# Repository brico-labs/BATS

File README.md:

NOTA IMPORTANTE  
Lee a sección [META](#meta) para clonar este proxecto.

Qué imos facer? Qué se describe en este documento?
==================================================

Imos deseñar un shield para Arduino usando [KiCad](http://www.kicad-pcb.org/)

Daremos unha visión xeral da funcionalidade da suite KiCad pero non vamos a redactar un tutorial detallado nin de deseño de circuitos nin do mesmo KiCad. Daremos as pistas xustiñas para empezar a traballar con KiCad, se queredes un tutorial detallado, en youtube tedes un super recomendable, elaborado por [TutoElectro](https://www.youtube.com/playlist?list=PL1Hs_F1k2mdRVYDtdWd7tQKDZTfxop7np)

Tamén comentaremos a nivel xeral os pasos para desenvolver este proxecto.

Qué é KiCad?
============

KiCad é unha suite de deseño electrónico automatizado [1]. KiCad permite o deseño tanto de esquemas de circuitos como das placas de circuito impreso a nivel profesional. A suite está dispoñible para Windows, Linux e Apple OS X. É un programa gratuito e **libre** distribuido baixo licencia **GNU GPL v2**.

Mellor ainda, a suite KiCad é a elexida polo CERN para o desenvolvemento e deseño de electrónica. É de esperar que con este respaldo a suite mellore ainda mais.

Requisitos do shield
====================

Queremos facer un shield que poida servir para iniciarse no mundo da programación con Arduino, especialmente centrado no ensino (tecnoloxía 3º - 4º ESO). Neste eido, traballar sobre breadboard pode ser complexo, moitas veces o material é compartido e isto implica que, cada clase, hai que montar e desmontar o circuito que logo se programará. Isto leva o seu tempo e ocasiona erros de montaxe que son difíciles de detectar, polo que o uso dun shield parece que pode ser unha solución.

Mália isto, empregando un shield xa ensamblada se perde a oportunidade de profundizar os coñecementos de electrónica e circuitos que se adquiren ao facer un mesmo a montaxe, así que un shield na que o alumno/a teña que colocar e soldar el mesmo os compoñentes, segundo avanza na súa aprendizaxe, parécenos a solución de compromiso idónea.

Queremos que o shield sexa escalable, que sirva para traballar cuns poucos compoñentes se non se quere profundizar demasiado, pero que permita tamén chegar a nivéis máis avanzados e con máis compoñentes sen cambiar de shield.

Estes son os compoñentes que se pensan incluír:

-   3-4 x Botóns
-   1 x RGB
-   1 x LDR
-   1 x Pines servo
-   1 x sensor temp (dudoso)
-   2 x potenciómetros
-   1 x LED vermello
-   1 x LED amarelo
-   1 x LED verde
-   1 x Zoador
-   1 x Botón de reset

Instalación de KiCad (en Ubuntu)
================================

Para instalar o KiCad en Ubuntu basta con facer o típico ciclo de instalación:

``` {bash}
sudo apt-get install kicad
```

Se queremos estar á última temos o ppa de Monsieur Reynaud dispoñible:

``` {bash}
sudo apt-add-repository ppa:js-reynaud/ppa-KiCad
sudo apt-get update
sudo apt-get install kicad
```

Nos escollimos esta opción.

Se non usades un linux baseado en Debian, teredes que consultar na rede como facer a instalación para o voso sistema operativo. De todolos xeitos a instalación é moi doada, donde podemos atopar algún problemiña é na instalación das bibliotecas de compoñentes que vos contaremos cos mais detalle mais adiante.

Configuración de directorios para este proxecto
===============================================

Además de desenvolver o proxecto con KiCad queremos ter o proxecto dispoñible en github.

Agora que temos KiCad instalado imos preparar un directorio de traballo ao que chamamos **bats**.

O directorio **bats** será o "repositorio" ou depósito do noso proxecto para git. Contén os seguintes subdirectorios:

doc  
Contén a documentación do proxecto (o que estás a leer agora mesmo) redactada en [Pandoc](http://pandoc.org/)

kicad  
Contén o proxecto KiCad

Unha vez que temos preparado o directorio do proxecto activamos git para iniciar o control de versións.

------------------------------------------------------------------------

Describir a configuración de git??

------------------------------------------------------------------------

Biblioteca de compoñentes incluindo un shield para Arduino
==========================================================

As bibliotecas de KiCad están organizadas en duas partes:

-   Un ficheiro que contén os símbolos dos compoñentes para usarse no editor de esquemas electrónicos **Eescheme**

-   As pegadas dos compoñentes electrónicos, é dicir, a forma que ten que ter a pista da placa de circuito impreso (*PCB*) para poder soldar o compoñente.

O KiCad trae por defecto varios templates que permiten o desenrolo de proxectos baseados en diferentes modelos de Arduino.

Nos optamos por outro camiño, instalamos unha nova biblioteca de compoñentes e fixemos o proxecto usando esta biblioteca.

Unha biblioteca moi completa é a de Freetronics que podemos atopar tamén en github en:

<https://github.com/freetronics/freetronics_KiCad_library.git>

As bibliotecas de KiCad poden estar almacenadas en diferentes directorios do noso ordenador. Poderíamos engadir as bibliotecas que usemos en algún subdirectorio de */usr/share/kicad* ou de */usr/local/share*. Esta podería ser unha boa estratexia nun servidor compartido por varios usuarios. Tamén poderíamos descarregar todas as bibliotecas a un directorio común do noso *home*. Pero como estamos facendo un control de versións do noso proxecto con git a propia páxina da biblioteca suxírenos o xeito mais adoitado de facer a instalación: coma un submódulo git do noso proxecto.

A vantaxe de engadir a biblioteca de compoñentes de Freetronics coma un submódulo Git é que o noso proxecto queda "aillado" do proxecto engadido como submódulo. Podemos avanzar no noso proxecto e salvar os cambios feitos con Git, sen afectar aos submódulos, e viceversa.

Por exemplo, unha vez que teñamos o noso directorio de traballo configurado con git, e a libreria de Freetronics engadida como submodulo, poderíamos empezar o desenrolo da nosa placa BATS e ir gardando os nosos avances. Estas operacións non afectarán a librería Freetronics, que de feito ainda que esta descarregada no noso directorio de traballo, non está gardada no git do noso proxecto, soamente está enlazada.

Se no futuro nos interesa actualizarnos a unha versión mais avanzada da librería Freetronics, podemos facer un commit do noso proxecto nunha situación controlada, e despois actualizar o submodulo correspondiente a librería.

Engadir a biblioteca como un submódulo de git
---------------------------------------------

Dende o directorio principal de noso proxecto descarregamos a biblioteca de Freetronics coma un submodulo do noso proxecto:

``` {bash}
cd kicad 
git submodule add https://github.com/freetronics/freetronics_kicad_library.git kicad/ftlibrary
```

Despois de engadir a biblioteca como un submódulo se consultamos o estado git do noso proxecto aparecerán dous novos ficheiros:

``` {bash}
$ git status
On branch master
Your branch is up-to-date with 'origin/master'.
Changes to be committed:
  (use "git reset HEAD <file>..." to unstage)

    new file:   .gitmodules
    new file:   kicad/ftlibrary
```

Git engadíu automáticamente os dous novos ficheiros, o directorio que contén a nosa biblioteca eo ficheiro **.gitmodule** que levará o control de todolos submódulos que usemos.

En realidade os ficheiros que compoñen a biblioteca non pertencen ao noso depósito de software, git só leva conta da versión da biblioteca de Freetronics que estamos a usar.

Se queres saber mais de esta potente funcionalidade de git podes leer: <http://www.git-scm.com/book/en/v2/Git-Tools-Submodules>

Configurar *Eescheme* para usar a nova biblioteca
-------------------------------------------------

No menú Preferences -&gt; Component Library sinalamos na fiestra inferior o directorio do noso proxecto. Na fiestra superior engadimos o ficheiro da biblioteca.

No github da biblioteca nos aconsellan poñer a biblioteca de primeira na nosa lista por que definen todo tipo de compoñentes. Nos de momento seguimos o consello de Freetronics, e a puxemos de primeira.

Configurar acceso aos datos de pegadas (*footprints*) en pcbnew
---------------------------------------------------------------

Configuramos un ficheiro para o noso proxecto declarando os *footprint* extra que imos a utilizar.

``` {cpp}
(fp_lib_table
  (lib
   (name FT)
   (type KiCad)
   (uri ${KIPRJMOD}/ftlibrary/freetronics_footprints.pretty)
   (options "")
   (descr "Freetronics Kicad Library")
   )
)
```

Engadimos o novo ficheiro ao noso repositorio

``` {bash}
git add fp-lib-table
```

Abrimos *Pcbnew* e no menú *Preferences-&gt;Footprint Libraries Manager* comprobamos que na pestaña *Project Specific Libraries* figura o noso ficheiro.

Tutorial
========

Checklist: Pasos a seguir para rematar o proxecto
-------------------------------------------------

-   Abrir o proxecto (e mellor tér un directorio dedicado ao proxecto creado en adianto)
-   Crear o esquema do circuito (usando Eescheme)
-   Chequeo de erros (opción *Perform Electrical Rules Check*)
-   Asignar as pegadas (*footprints*) aos compoñentes (opción *run CvPcb* dende o *Eescheme*). As pegadas quedan asignadas a cada compoñente no esquema.
-   Xerar o ficheiro NET (opción *Generate netlist*)
-   Abrir o PcbNew e cargar o ficheiro NET xenerado dende o Eescheme
-   Distribuir os compoñentes do noso proxecto intentado simplificar a topoloxía das pistas o que poidamos.

A pantalla xeral
----------------

------------------------------------------------------------------------

Pantalla xeral de KiCad opcións, citar a lista de hotkeys

------------------------------------------------------------------------

Abrindo un proxecto
-------------------

### Checklist

-   Usar un directorio adicado ao proxecto
-   Engadir a información do proxecto ao esquema.

Abrimos un novo proxecto: File::New Project (Ctrl+N) **bats**

### 

Crear e Editar o esquema do circuito
------------------------------------

O primeiro que imos facer é o esquema do circuito. Para isto temos que usar a ferramenta *Eeschema* que podemos atopar en tres lugares diferentes [2] na barra de iconos de ferramentas, no menú de KiCad no título da fiestra, ou có atallo **Ctrl+E**.

Abrimos eescheme e creamos un novo ficheiro de esquema.

ERC: comprobación dos erros no circuito
---------------------------------------

### Tips

-   Falar dos flags
    -   Power flags
    -   Not used flag
-   Falar dos ficheiros de pegadas
-   Falar da asignación automática de pegadas

As bibliotecas en KiCAD
=======================

Esta é sen dúbida a parte de KiCAD mais criticada. Hai varias razóns para isto:

-   As bibliotecas de KiCAD manteñen separados os símbolos dos compoñentes para usar no esquema do circuito das pegadas (*footprints*) dos mesmos que son os que se usan no deseño da placa.
-   Os símbolos dos compoñentes están almacenados en ficheiros con extensión *.lib* de ahí que con frecuencia se lles chame *library* (traducido librerias) na xerga de KiCAD
-   Por contra as pegadas dos compoñentes almacénanse en ficheiros con extensión *.mod* ou as mais modernas *.kicad\_mod* de ahí que a miudo se lles chame *modules* (traducido módulos) na xerga de KiCAD
-   Os menús e diálogos para engadir ficheiros *.lib* e os ficheiros *.mod* son completamente diferentes
-   KiCAD soporta multiples localizacións para as bibliotecas, mesmo localizacións en github.

Dende o noso punto de vista o mais sinxelo e ter un só directorio donde almacenemos as bibliotecas de terceiros que queremos usar con KiCAD. Nos usamos **~/resources/kicad** de feito temos:

~/resources/kicad/my\_kicad\_lib  
Para os compoñentes de diseño propio

~/resources/kicad/my\_kicad.pretty  
para os footprints de diseño propio

~/resources/kicad/kicad\_3rd  
para librerias de terceiros

Un exemplo: Engadir novas bibliotecas Arduino
---------------------------------------------

Imos ver como engadir unha nova biblioteca de compoñentes de xeito global (quedará dispoñible para todos os proxectos) ou só para un proxecto concreto.

As bibliotecas que imos usar pódense atopar en esta [páxina](http://meta-blog.eklablog.com/kicad-librairie-arduino-pretty-p930786).

Na páxina hai dous ficheiros dispoñibles para descarga. O que contén as plantillas (*templates*) non o queremos, xa está incluido no github de KiCAD.

Descarregamos o outro e descomprimimos no directorio donde imos ter as bibliotecas de KiCAD, no noso caso: **~/resources/kicad/kicad\_3rd**

Enlaces útiles
==============

-   [Conceptos de circuitos impresos](http://www.pcb.electrosoft.cl/04-articulos-circuitos-impresos-desarrollo-sistemas/01-conceptos-circuitos-impresos/conceptos-circuitos-impresos-pcb.html)
-   [Instalación das bibliotecas](http://www.arunet.co.uk/tkboyd/ele2pcbka.htm)
-   [Mais bibliotecas para KiCad](http://www.kicadlib.org/)

Dende o seguinte enlace podese descarregar unha biblioteca de compoñentes moi currada, ainda que algo anticuada:

<git://smisioto.eu/KiCad_libs.git>

META
====

Este repositorio usa submódulos de git para a xestión das bibliotecas de compoñentes. Para clonar o repositorio tes que clonar o repositorio e despois actualizar os submódulos executando:

``` {bash}
$ git clone https://github.com/brico-labs/BATS
$ git submodule update --init
```

Este documento está escrito en [Markdown-Pandoc](http://pandoc.org/README.html). Pandoc e un sistema moi sinxelo de documentación que permite xerar multiples formatos de saída.

As fontes do documento están no directorio **doc/src**. Os formatos de saída son este fichero **README.md** en formato Markdown-github e os documentos que podes atopar no directorio **doc/out** incluindo un pdf.

Os documentos xéranse automáticamente a partir do ficheiro fonte sen mais que executar:

``` {bash}
$ cd doc
$ make
```

Outras opcións que soporta o **makefile** serían **reset** para rexerar todos os documentos de saída por defecto, **odt** para xerar un **bats\_gl.odt**.

``` {bash}
$ make reset
$ make odt
```

[1] EDA suite en inglés

[2] Isto de ter varios xeitos de facer unha cousa é habitual en KiCad como iremos vendo

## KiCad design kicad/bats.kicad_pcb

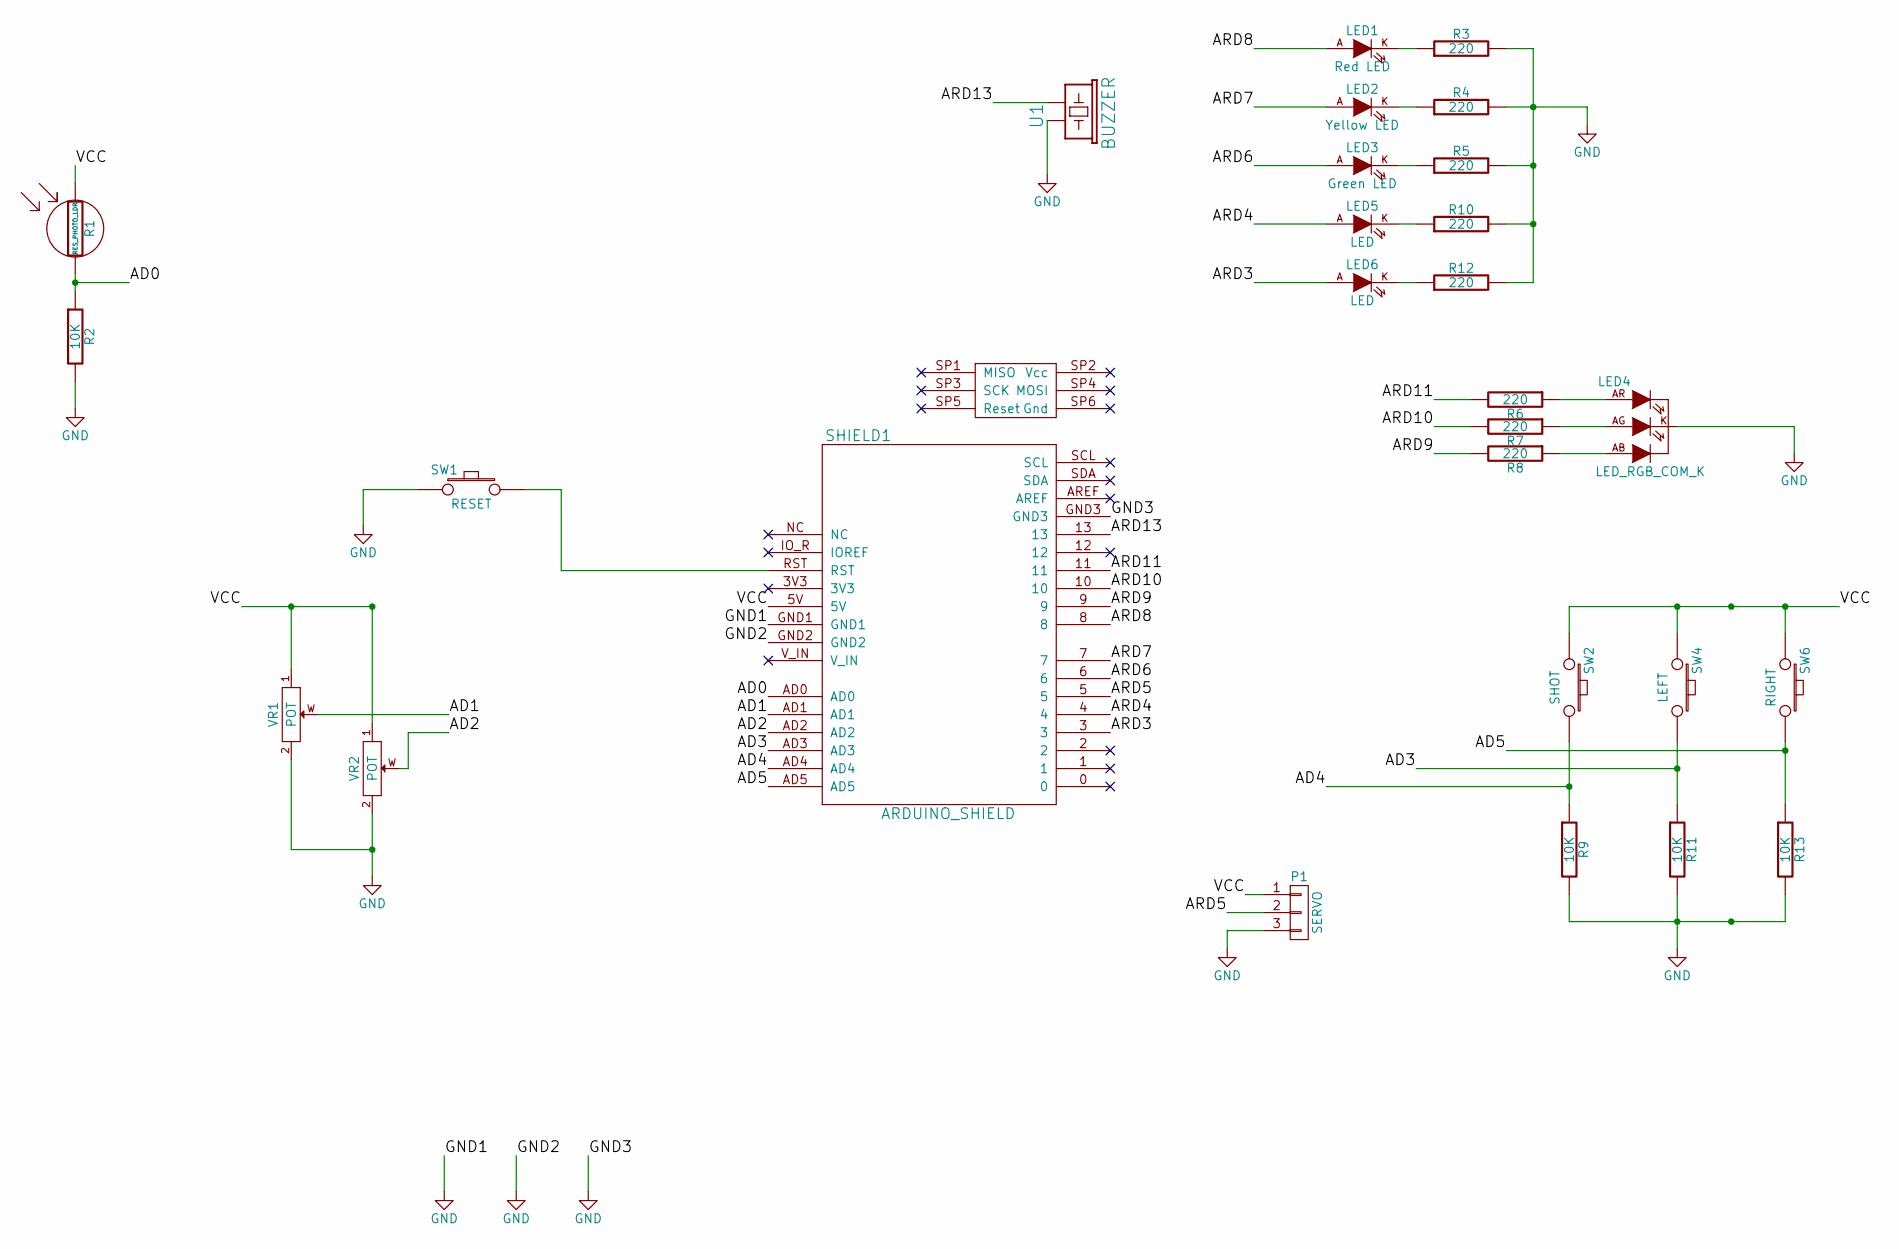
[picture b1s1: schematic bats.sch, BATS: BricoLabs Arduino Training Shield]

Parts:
LED1: Red LED; LED-5MM_easy_soldering
LED2: Yellow LED; LED-5MM_easy_soldering
LED3: Green LED; LED-5MM_easy_soldering
LED4: LED_RGB_COM_K; LED-RGB-8MM-COM-K-MINIMAL
LED5, LED6: LED; LED-5MM_easy_soldering
P1: SERVO; 1X03
R1: RES_PHOTO_LDR; Resistor_Horizontal_SmallHole_RM10mm
R2, R9, R11, R13: 10K; Resistor_Horizontal_SmallHole_RM10mm
R3, R4, R5, R6, R7, R8, R10, R12: 220; Resistor_Horizontal_SmallHole_RM10mm
SHIELD1: ARDUINO_SHIELD
SW1: RESET; SW_PUSHBUTTON_PTH
SW2: SHOT; SW_PUSHBUTTON_PTH
SW4: LEFT; SW_PUSHBUTTON_PTH
SW6: RIGHT; SW_PUSHBUTTON_PTH
U1: BUZZER; Buzzer_12x9.5RM7.6
VR1, VR2: POT; POT_RV09_VERT_easySoldering

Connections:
/AD0: R1.2, R2.1, SHIELD1.AD0
/AD1: SHIELD1.AD1, VR1.W
/AD2: SHIELD1.AD2, VR2.W
/AD3: R11.1, SHIELD1.AD3, SW4.2
/AD4: R9.1, SHIELD1.AD4, SW2.2
/AD5: R13.1, SHIELD1.AD5, SW6.2
/ARD3: LED6.A, SHIELD1.3
/ARD4: LED5.A, SHIELD1.4
/ARD5: P1.2, SHIELD1.5
/ARD6: LED3.A, SHIELD1.6
/ARD7: LED2.A, SHIELD1.7
/ARD8: LED1.A, SHIELD1.8
/ARD9: R8.2, SHIELD1.9
/ARD10: R7.2, SHIELD1.10
/ARD11: R6.2, SHIELD1.11
/ARD13: SHIELD1.13, U1.2 (GND)
/VCC: P1.1, R1.1, SHIELD1.5V, SW2.1, SW4.1, SW6.1, VR1.1, VR2.1
GND: LED4.K, P1.3, R2.2, R3.2, R4.2, R5.2, R9.2, R10.2, R11.2, R12.2, R13.2, SHIELD1.GND1, SHIELD1.GND2, SHIELD1.GND3, SW1.1, U1.1 (POS), VR1.2, VR2.2
unnamed: LED1.K, R3.1
unnamed: LED2.K, R4.1
unnamed: LED3.K, R5.1
unnamed: LED4.AB, R8.1
unnamed: LED4.AG, R7.1
unnamed: LED4.AR, R6.1
unnamed: LED5.K, R10.1
unnamed: LED6.K, R12.1
unnamed: SHIELD1.RST, SW1.2

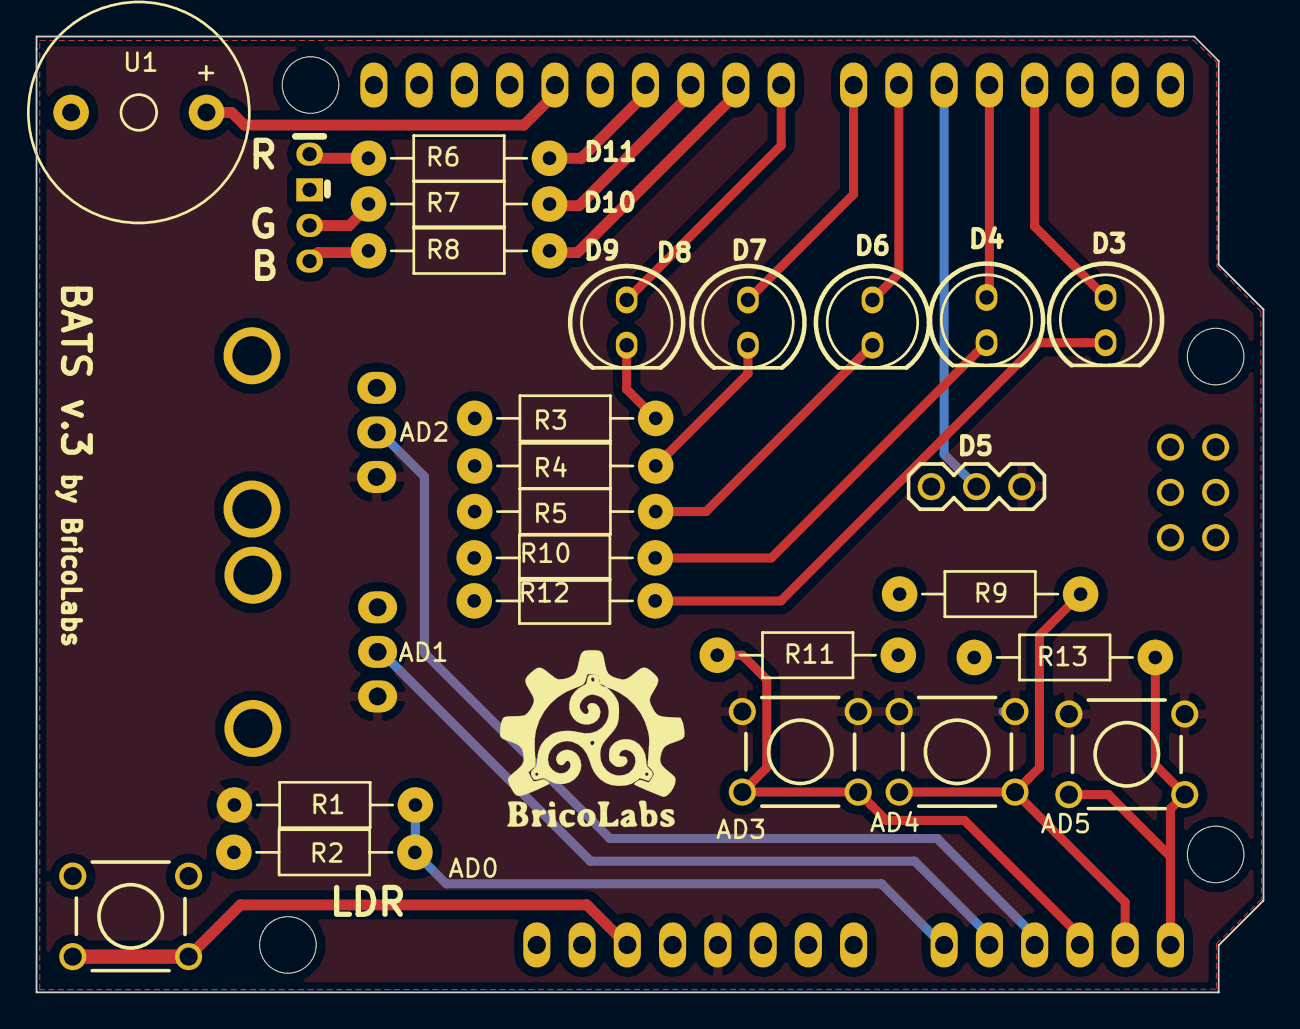
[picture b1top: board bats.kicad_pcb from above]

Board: 2 copper layers, 68.9 x 53.6 mm, 28 parts (0 on the bottom side), 27 nets.

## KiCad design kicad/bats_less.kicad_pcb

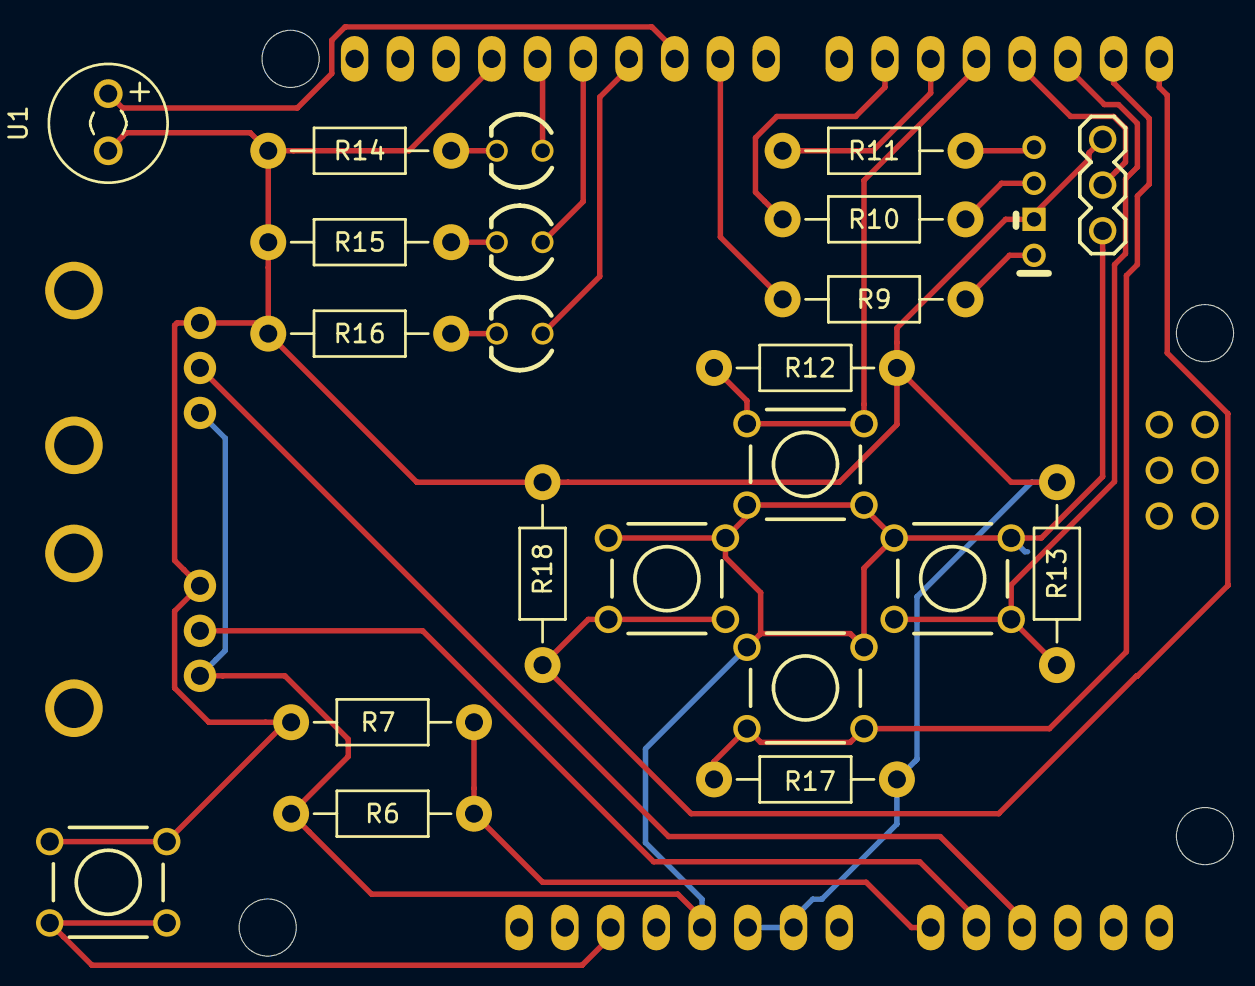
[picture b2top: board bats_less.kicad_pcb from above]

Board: 2 copper layers, 26 parts (0 on the bottom side), 24 nets.

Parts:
LED1: Red LED; LED-3MM
LED2: Yellow LED; LED-3MM
LED3: Green LED; LED-3MM
LED4: LED_RGB_COM_K; LED-RGB-8MM-COM-K-MINIMAL
P1: SERVO; 1X03
R6: RES_PHOTO_LDR; Resistor_Horizontal_RM10mm
R7: 1K; Resistor_Horizontal_RM10mm
R9, R10, R11: 220; Resistor_Horizontal_RM10mm
R12, R13, R17, R18: 10K; Resistor_Horizontal_RM10mm
R14, R15, R16: 470; Resistor_Horizontal_RM10mm
SHIELD1: ARDUINO_SHIELD
SW5: RESET; SW_PUSHBUTTON_PTH
SW6: UP; SW_PUSHBUTTON_PTH
SW7: LEFT; SW_PUSHBUTTON_PTH
SW8: DOWN; SW_PUSHBUTTON_PTH
SW9: RIGHT; SW_PUSHBUTTON_PTH
U1: BUZZER; MagneticBuzzer_Kingstate_KCG0601
VR1, VR2: POT; POT_RV09_VERT

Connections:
GND: LED4.K, P1.3, R7.2, R12.2, R13.2, R14.2, R15.2, R16.2, R17.2, R18.2, SHIELD1.GND1, SHIELD1.GND2, SHIELD1.GND3, SW5.1, U1.1, VR1.2, VR2.2
unnamed: LED1.A, SHIELD1.13
unnamed: LED1.K, R14.1
unnamed: LED2.A, SHIELD1.12
unnamed: LED2.K, R15.1
unnamed: LED3.A, SHIELD1.11
unnamed: LED3.K, R16.1
unnamed: LED4.AB, R11.1
unnamed: LED4.AG, R10.1
unnamed: LED4.AR, R9.1
unnamed: P1.1, R6.1, SHIELD1.5V, SW6.1, SW7.1, SW8.1, SW9.1, VR1.1, VR2.1
unnamed: P1.2, SHIELD1.3
unnamed: R6.2, R7.1, SHIELD1.AD0
unnamed: R9.2, SHIELD1.9
unnamed: R10.2, SHIELD1.6
unnamed: R11.2, SHIELD1.5
unnamed: R12.1, SHIELD1.4, SW6.2
unnamed: R13.1, SHIELD1.2, SW7.2
unnamed: R17.1, SHIELD1.1, SW8.2
unnamed: R18.1, SHIELD1.0, SW9.2
unnamed: SHIELD1.10, U1.2
unnamed: SHIELD1.AD1, VR1.W
unnamed: SHIELD1.AD2, VR2.W
unnamed: SHIELD1.RST, SW5.2

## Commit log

2015-06-20 Primer "commit": versións iniciáis dos ficheiros.
2015-06-21 Engadida a biblioteca de Freetronics
2015-06-21 Algunha corrección ortográfica
2015-06-21 Engadida a sección META á documentación
2015-06-21 Primeiros pasos có esquema * Engadido o shield arduino * Engadidos tres leds coas suas resistencias * Asignados footprints a todos os compoñentes
2015-06-22 Engadido o LDR Algún cambio na documentación
2015-06-22 Salvados cambios no proxecto despois de engadir o LDR
2015-06-22 Cambiado o nome do shield na documentación
2015-06-23 Creado o novo proxecto kicad con nome correcto: bats
    Resulta que cambiar o nome do proxecto en KiCAD non é nada doado.
2015-06-23 Borrados os restantes ficheiros con nome sandboxShield Engadido algún compoñente mais
2015-06-23 Cambiados os nomes dos ficheiros de documentos a bats
2015-06-23 Amañadas as listas de definición na documentación
2015-06-24 Mais avances no esquema do circuito
2015-06-24 Algún cambio mais.
2015-06-24 Engadido o ficheiro net ao github
2015-06-24 Update README.md
    engadida xustificación pedagóxica
2015-06-24 Engadido o esquema en formato pdf
2015-06-25 Cambios no ficheiro de documentación.
    Cambiado a orden de execución dos programas no checklist
2015-06-25 A PCB empeza a coller forma.
2015-09-04 Mais cambios non especificados, facemos o commit antes de borrar o conxunto de pulsadores analóxicos.
2015-09-05 Cambiado o footprint dos potes. Todos os compoñentes situados na placa Mínimos cambios na documentación (engadida breve explicación dos submódulos de git)
2015-09-05 Engadido o zip do proxecto xerado dende KiCAD
2015-09-05 Minor changes in documentation
2015-09-05 Primeira versión enrutada, ainda precisa duas caras, hai que pensar un pouco mais.
2015-09-06 Engadida unha "KiCAD cheat sheet", una chuleta para KiCAD, non rematada
    Engadida unha segunda versión da placa intentando deixar todo nunha
    cara.
2015-09-06 Engadido logo de BricoLabs na chuleta de KiCAD
2015-10-15 Un commit intermedio facendo probas
2015-10-15 Recolocados casi todos os compoñentes Simplificado esquema Aumentado o ancho de pistas
2015-10-16 Casi rematado
2015-10-19 Colocadas as esquiñas da zona de recheo de masa.
2015-10-20 Engadida area de recheo no fronte da placa
2015-10-20 PCB en versión PDF
2015-11-14 Correxida a forma da placa Correxida a posición do botón de reset Correxida a posición do nome da placa
2015-11-14 Engadidos Silks de probas Limpeza de directorios Exportados Gerber
2015-11-14 Cambios menores na placa
2015-11-14 Salvado o estado global do proxecto
2015-11-14 Exportados os Gerber files, preparado un zip cós Gerber para facer un pedido.
2015-11-15 Cambiado ficheiro zip cos grb para o pedido a DirtyPCB Pedido feito
2015-12-13 Engadida mais información da xestión de Bibliotecas
2015-12-13 Arranxado algún erro de composición
2015-12-15 Borrados os simbolos de alineamiento que se transformaron en vias en dirtypcb
    Algo mais de documentación.
2016-01-05 Cambios masivos:
    Issue 01 - Cambiados os botóns de D0 e D1 a AD4 e AD5 respectivamente.
    Issue 02 - Cambiada a posición dos dous potes e do led rgb cara ao
    interior da placa.
    Issue 05 - Serigrafiados os pines de control
    Issue 06 - Sustituido o buzzer
    Además simplifícase todo o enrutado da placa.
2016-01-25 Engadimos algunha serigrafía mais. Todo semella estar listo para a segunda versión.
2016-01-26 Exported new gerber files
2016-03-30 Cambiamos o método de xerar os doc, agora usamos make
    Cambiadas opcións de formato na documentación pdf para dar un estilo
    mais moderno.
    Engadida documentación en formato epub.
    Engadidas as opcións para xerar formato odt e mediawiki.
2016-03-30 Correxido erro na sección META da documentación
2016-04-03 Cambiadas algunhas pistas para reconectar as areas positivas do frontal
2016-04-03 Correxida a posición do polo positivo na silk do zoador.
2016-04-03 Cambiada a posición da rotulación do polo positivo no zoador.
2016-04-03 Engadida unha conexión extra na area positiva.
2016-04-03 Salvado o proxecto, que me esquecía
2016-04-30 Cambiadas as pegadas das resistencias a furados mais pequenos.
2016-05-14 Cambiados os LED a LED de 5mm no esquema e mais no ficheiro net
2016-05-14 - Correxida a posición da rotulacion de todas as resistencias - Cambiada o tamaño dos leds a 5 mm, cambia tamén a sua posición, pecha o issue #4 - Cambiada a posición de resistencias R3, R4 e R5 e ma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
2016-05-14 Versión 2.1, non é outra cousa que a versión 2.0 cos erros correxidos
2016-05-23 Primeira versión con tres botóns. Ten pistas redundantes e hai que cambiar os pines dos botóns.
2016-05-23 Salvado o proxecto
2016-05-23 Amañados os terminais dos botóns Compre rotar os botóns para simplificar as pistas
2016-05-23 TEN UN FALLO, non usar sen cambiar o botón en D1
2016-05-24 Primeira versión completa con tres botóns. Os ficheiros gerber non son válidos. - Hai que revisar a conexión do servo - Hai que alinear ben os tres botóns
2016-06-21 Todo listo para facer pedido a dirtypcb
2016-11-19 Algun cambio na documentación
2016-11-20 Algún pequeno cambio na documentación.
2016-11-25 Engadida a documentación para o taller da OSHWDem
2016-11-26 Engadidos os programas de exemplo
2017-03-22 Engadida a biblioteca KiCAD de BricoLabs coma submodule
2017-09-23 Engadidas as novas pisadas "easy soldering" dende a biblioteca KiCAD de BricoLabs Actualizados os submódulos
2017-09-24 Cambiadas as posicións dos botóns
2017-09-27 Rematadas as ultimas modificacións
2017-09-27 Todos os cambios previos a OSHWDem-2017 rematados
2017-09-27 Revisados adornos dos silks e números de versións
2017-09-27 Todo listo para facer pedido OSHWDem-2017
